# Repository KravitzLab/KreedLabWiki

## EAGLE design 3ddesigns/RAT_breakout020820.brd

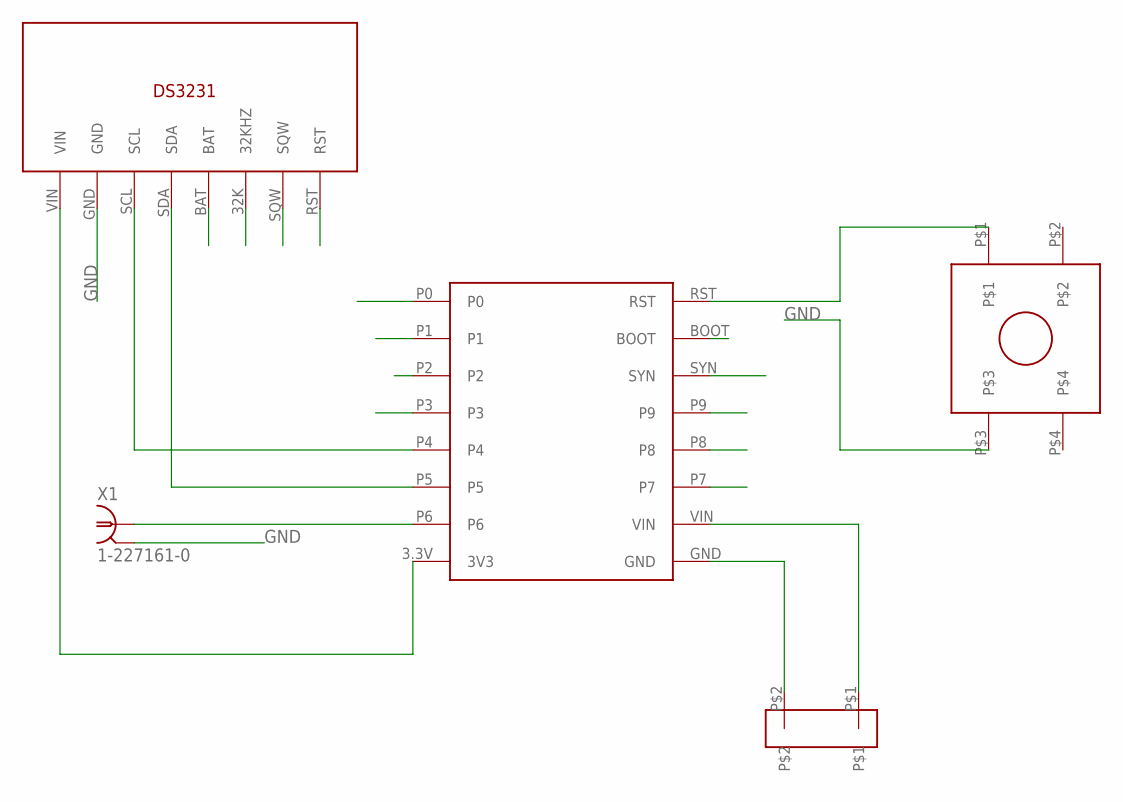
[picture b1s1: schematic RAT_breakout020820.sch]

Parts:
U$1: OPENMV_M7
U$2: JST_RA_PRT-09749
U$3: BTN_COM-10302
U$6: DS3231-RTC
X1: 1-227161-0; AMP_227161

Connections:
GND: U$1.GND, U$2.P$2, U$3.P$3, U$6.GND, X1.2
unnamed: U$1.RST, U$3.P$1
unnamed: U$1.VIN, U$2.P$1
unnamed: U$1.P6, X1.1
unnamed: U$1.3.3V (3V3), U$6.VIN
unnamed: U$1.P4, U$6.SCL
unnamed: U$1.P5, U$6.SDA

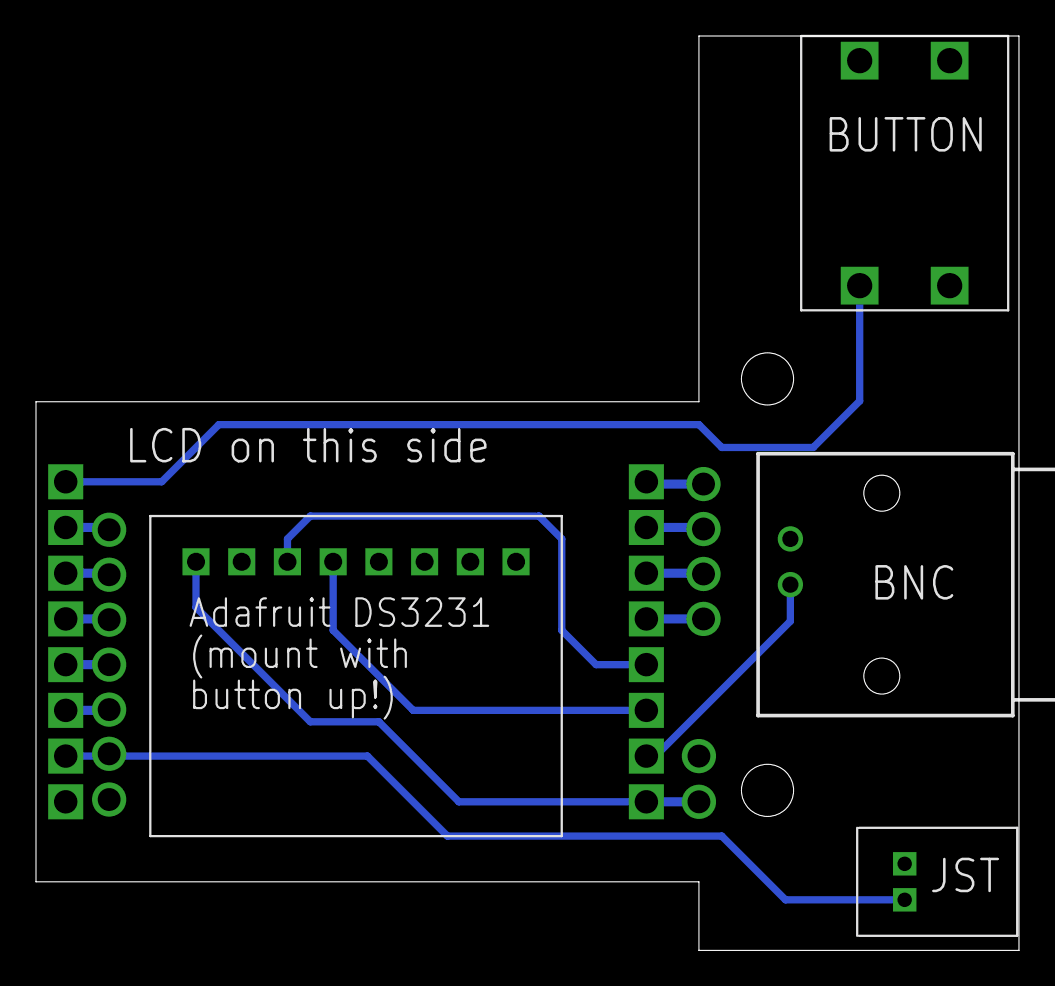
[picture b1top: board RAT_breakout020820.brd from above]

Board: 2 copper layers, 54.6 x 50.8 mm, 7 parts (1 on the bottom side), 7 nets.

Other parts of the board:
U$4, U$5: 4-40_HOLE

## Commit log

2023-09-15 deleted docx files
2024-10-25 Create PR-Code-Task-FED3
2024-10-25 Update and rename PR-Code-Task-FED3 to PR-Code-Task-FED3-Advanced
2024-10-25 Create PR-Task-Code-Basic parameters
2025-01-22 Create Bandit-Task-Analysis to process data files
2025-01-22 Bandit-Task-Analysis to process data files
2025-01-22 Create Bandit-Task plot results (boxplots)
2025-01-22 Bandit-Task plot results (boxplots)
2025-03-25 updated examples
2025-04-22 Create RTPP
2025-07-22 DCM Card Access Request Form
2025-10-30 Add files via upload
    HFD and Prox Mice Code
2025-10-30 Add files via upload
    HFD Easy Hard Excel File for Code
2025-10-30 Add files via upload
    Code for HFD and Prox Experiment
2025-12-03 Created using Colab
2025-12-03 Added mouse transfer forms
2026-02-20 Move photometry notebook to PythonNotebooks
    Remove the duplicate Photometry_preprocessing.ipynb from the repository root and keep the notebook in the PythonNotebooks directory. This reorganizes notebooks into the PythonNotebooks folder; the no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
2026-03-11 added BanditCode with Recording output
2026-03-12 UpdatedBanditRecordingCode
